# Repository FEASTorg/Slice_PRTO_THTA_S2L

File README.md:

# Prototyping Slice

THT Array/All.

BREAD slice for creating new BREAD slices.

## Introduction

[Short introduction on the project.]

## Usage

[Explain how to use the project. Include examples and screenshots if applicable.]

## Documentation

Please refer to the [docs](/docs) for more info.

---

<div align="center">
  
</div>

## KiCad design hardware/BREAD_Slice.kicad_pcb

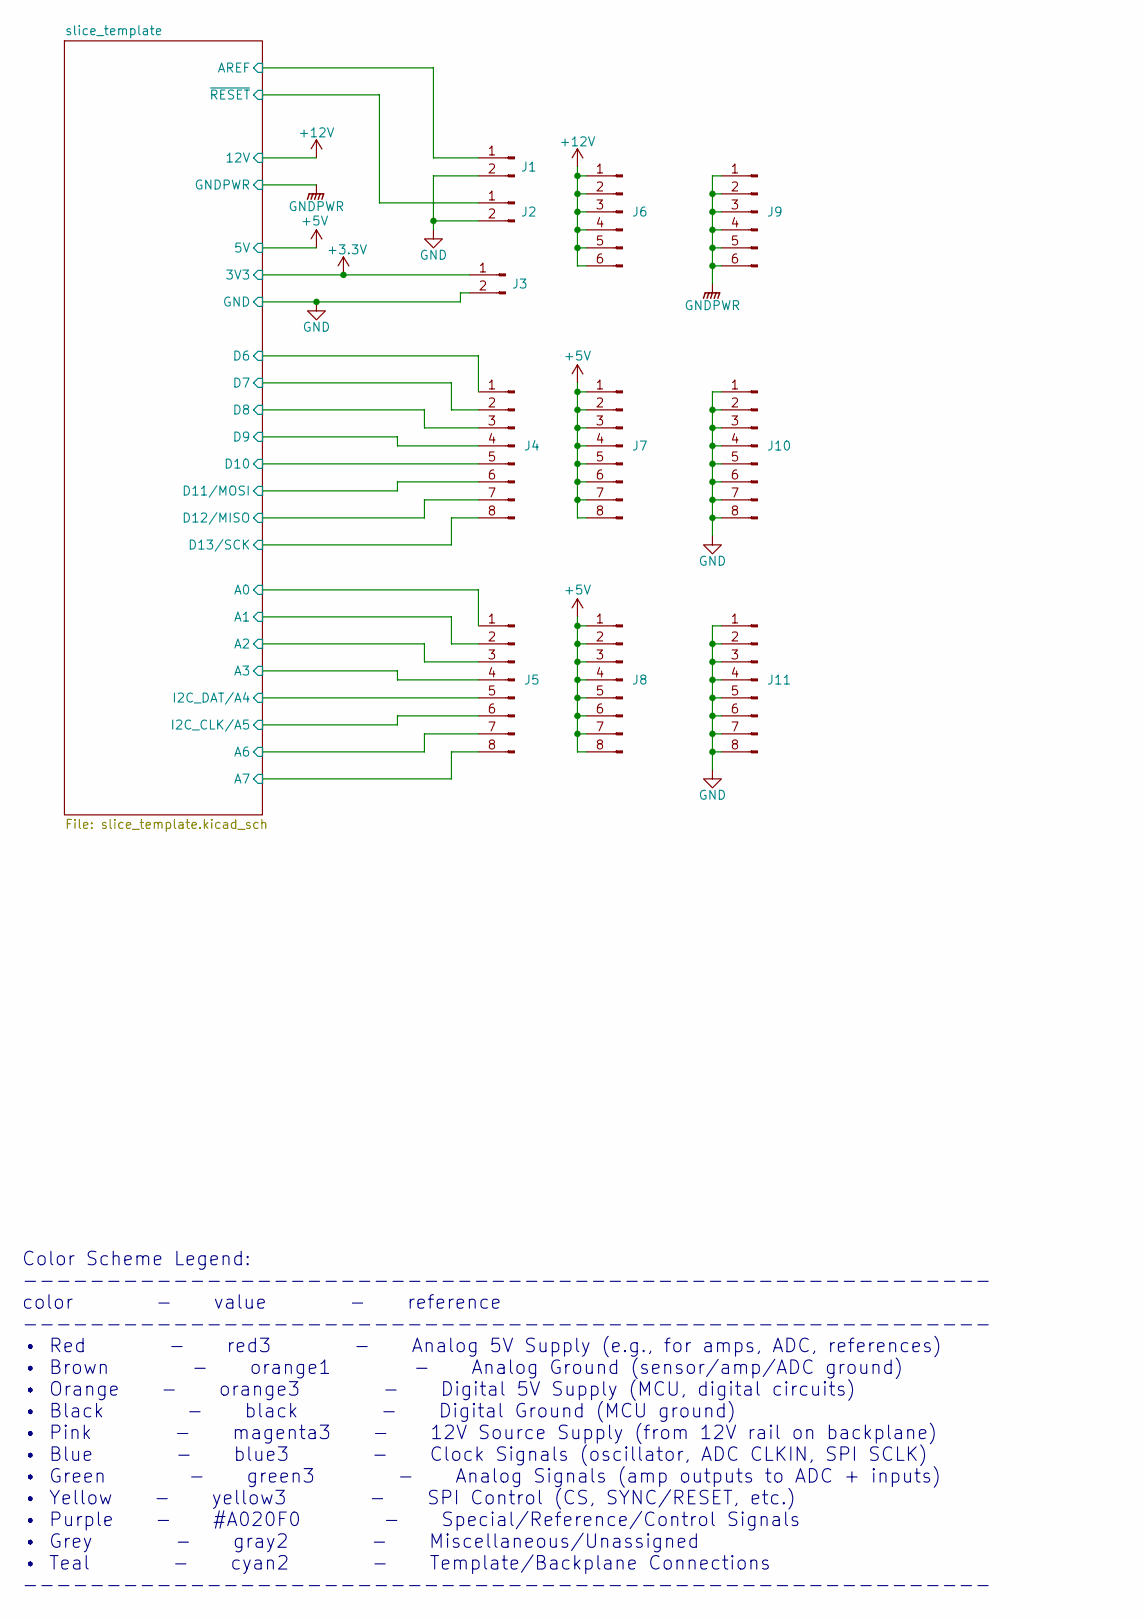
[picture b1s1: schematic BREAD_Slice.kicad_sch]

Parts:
J1, J2, J3: Conn_01x02_Pin; PinHeader_1x02_P2.54mm_Vertical
J4, J5, J7, J8, J10, J11: Conn_01x08_Pin; PinHeader_1x08_P2.54mm_Vertical
J6, J9: Conn_01x06_Pin; PinHeader_1x06_P2.54mm_Vertical

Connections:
+3.3V: J3.1; also elsewhere on the board
+5V: J7.1, J7.2, J7.3, J7.4, J7.5, J7.6, J7.7, J7.8, J8.1, J8.2, J8.3, J8.4, J8.5, J8.6, J8.7, J8.8; also elsewhere on the board
+12V: J6.1, J6.2, J6.3, J6.4, J6.5, J6.6; also elsewhere on the board
/slice_template/A0: J5.1; also elsewhere on the board
/slice_template/A1: J5.2; also elsewhere on the board
/slice_template/A2: J5.3; also elsewhere on the board
/slice_template/A3: J5.4; also elsewhere on the board
/slice_template/A6: J5.7; also elsewhere on the board
/slice_template/A7: J5.8; also elsewhere on the board
/slice_template/AREF: J1.1; also elsewhere on the board
/slice_template/D6: J4.1; also elsewhere on the board
/slice_template/D7: J4.2; also elsewhere on the board
/slice_template/D8: J4.3; also elsewhere on the board
/slice_template/D9: J4.4; also elsewhere on the board
/slice_template/D10: J4.5; also elsewhere on the board
/slice_template/D11/MOSI: J4.6; also elsewhere on the board
/slice_template/D12/MISO: J4.7; also elsewhere on the board
/slice_template/D13/SCK: J4.8; also elsewhere on the board
/slice_template/I2C_CLK/A5: J5.6; also elsewhere on the board
/slice_template/I2C_DAT/A4: J5.5; also elsewhere on the board
/slice_template/~RESET: J2.1; also elsewhere on the board
GND: J1.2, J2.2, J3.2, J10.1, J10.2, J10.3, J10.4, J10.5, J10.6, J10.7, J10.8, J11.1, J11.2, J11.3, J11.4, J11.5, J11.6, J11.7, J11.8; also elsewhere on the board
GNDPWR: J9.1, J9.2, J9.3, J9.4, J9.5, J9.6; also elsewhere on the board

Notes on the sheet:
Color Scheme Legend: ---------------------------------------------------------- color - value - reference ---------------------------------------------------------- • Red - red3 - Analog 5V Supply (e.g., for amps, ADC, references) • Brown - orange1 - Analog Ground (sensor/amp/ADC ground) • Orange -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

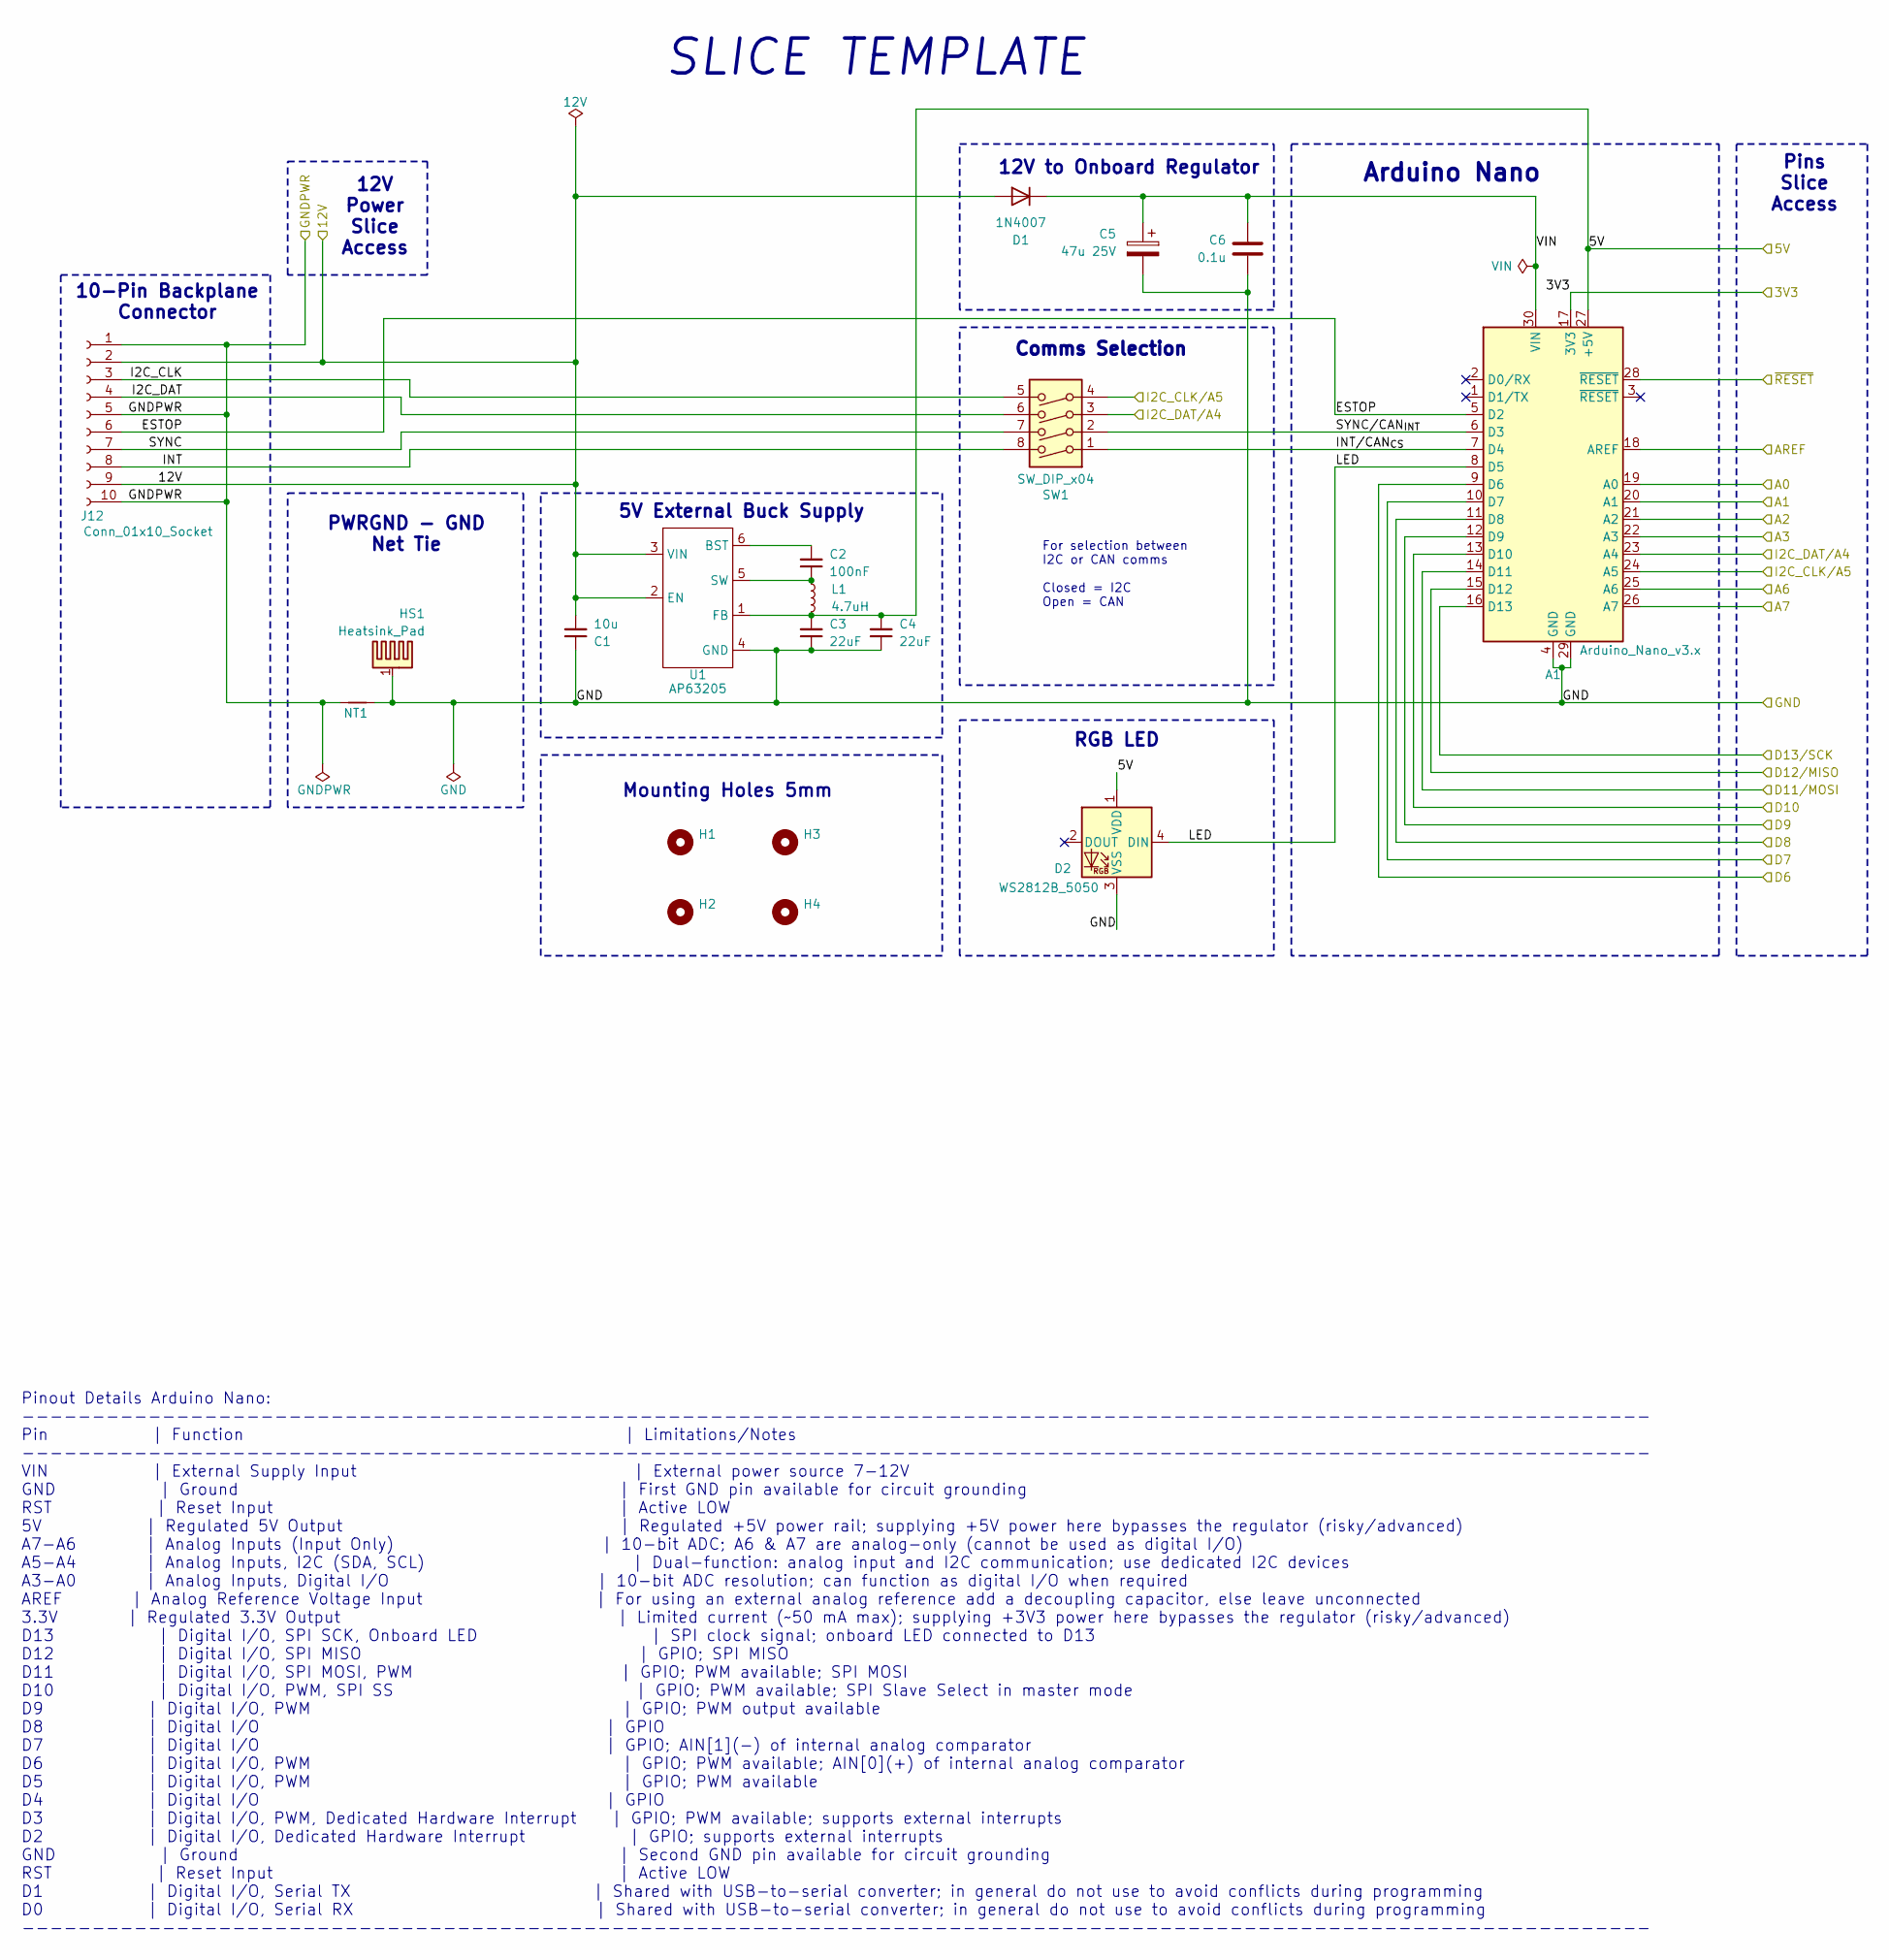
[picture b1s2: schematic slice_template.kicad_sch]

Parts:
A1: Arduino_Nano_v3.x; Arduino_Nano_Headers
C1: 10u; C_1206_3216Metric
C2: 100nF; C_1206_3216Metric
C3, C4: 22uF; C_1206_3216Metric
C5: 47u 25V; CP_Elec_6.3x7.7
C6: 0.1u; C_0805_2012Metric_Pad1.18x1.45mm_HandSolder
D1: 1N4007; D_SOD-123F
D2: WS2812B_5050; WS2812-5050-4PIN
H1, H2, H3, H4: MountingHole; MountingHole_5mm
HS1: Heatsink_Pad; Thermal_Pad
J12: Conn_01x10_Socket; PinSocket_1x10_P2.54mm_Horizontal
L1: 4.7uH; L_1210_3225Metric
NT1: NetTie_2; NetTie-2_SMD_Pad2.0mm
SW1: SW_DIP_x04; SW_DIP_SPSTx04_Slide_9.78x12.34mm_W8.61mm_P2.54mm
U1: AP63205; SOIC_05WU-7_DIO

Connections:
+3.3V: A1.17 (3V3); also elsewhere on the board
+5V: A1.27 (+5V), C3.2, C4.2, D2.1 (VDD), L1.2, U1.1 (FB); also elsewhere on the board
+12V: C1.2, D1.2 (A), J12.2, J12.9, U1.2 (EN), U1.3 (VIN); also elsewhere on the board
/slice_template/A0: A1.19 (A0); also elsewhere on the board
/slice_template/A1: A1.20 (A1); also elsewhere on the board
/slice_template/A2: A1.21 (A2); also elsewhere on the board
/slice_template/A3: A1.22 (A3); also elsewhere on the board
/slice_template/A6: A1.25 (A6); also elsewhere on the board
/slice_template/A7: A1.26 (A7); also elsewhere on the board
/slice_template/AREF: A1.18 (AREF); also elsewhere on the board
/slice_template/D6: A1.9 (D6); also elsewhere on the board
/slice_template/D7: A1.10 (D7); also elsewhere on the board
/slice_template/D8: A1.11 (D8); also elsewhere on the board
/slice_template/D9: A1.12 (D9); also elsewhere on the board
/slice_template/D10: A1.13 (D10); also elsewhere on the board
/slice_template/D11/MOSI: A1.14 (D11); also elsewhere on the board
/slice_template/D12/MISO: A1.15 (D12); also elsewhere on the board
/slice_template/D13/SCK: A1.16 (D13); also elsewhere on the board
/slice_template/ESTOP: A1.5 (D2), J12.6
/slice_template/I2C_CLK: J12.3, SW1.5
/slice_template/I2C_CLK/A5: A1.24 (A5), SW1.4; also elsewhere on the board
/slice_template/I2C_DAT: J12.4, SW1.6
/slice_template/I2C_DAT/A4: A1.23 (A4), SW1.3; also elsewhere on the board
/slice_template/INT: J12.8, SW1.8
/slice_template/INT/CAN_{CS}: A1.7 (D4), SW1.1
/slice_template/LED: A1.8 (D5), D2.4 (DIN)
/slice_template/SYNC: J12.7, SW1.7
/slice_template/SYNC/CAN_{INT}: A1.6 (D3), SW1.2
/slice_template/VIN: A1.30 (VIN), C5.1, C6.1, D1.1 (K)
/slice_template/~RESET: A1.28 (~RESET); also elsewhere on the board
GND: A1.4 (GND), A1.29 (GND), C1.1, C3.1, C4.1, C5.2, C6.2, D2.3 (VSS), HS1.1, NT1.1, U1.4 (GND); also elsewhere on the board
GNDPWR: J12.1, J12.5, J12.10, NT1.2; also elsewhere on the board
unnamed: C2.2, U1.6 (BST)
unnamed: C2.1, L1.1, U1.5 (SW)

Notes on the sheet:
Pins Slice Access
10-Pin Backplane Connector
PWRGND - GND Net Tie
SLICE TEMPLATE
RGB LED
Pinout Details Arduino Nano: -------------------------------------------------------------------------------------------------------------------- Pin | Function | Limitations/Notes -------------------------------------------------------------------------------------------------------------------- V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
Comms Selection
Mounting Holes 5mm
12V Power Slice Access
For selection between I2C or CAN comms Closed = I2C Open = CAN
Arduino Nano
12V to Onboard Regulator
5V External Buck Supply

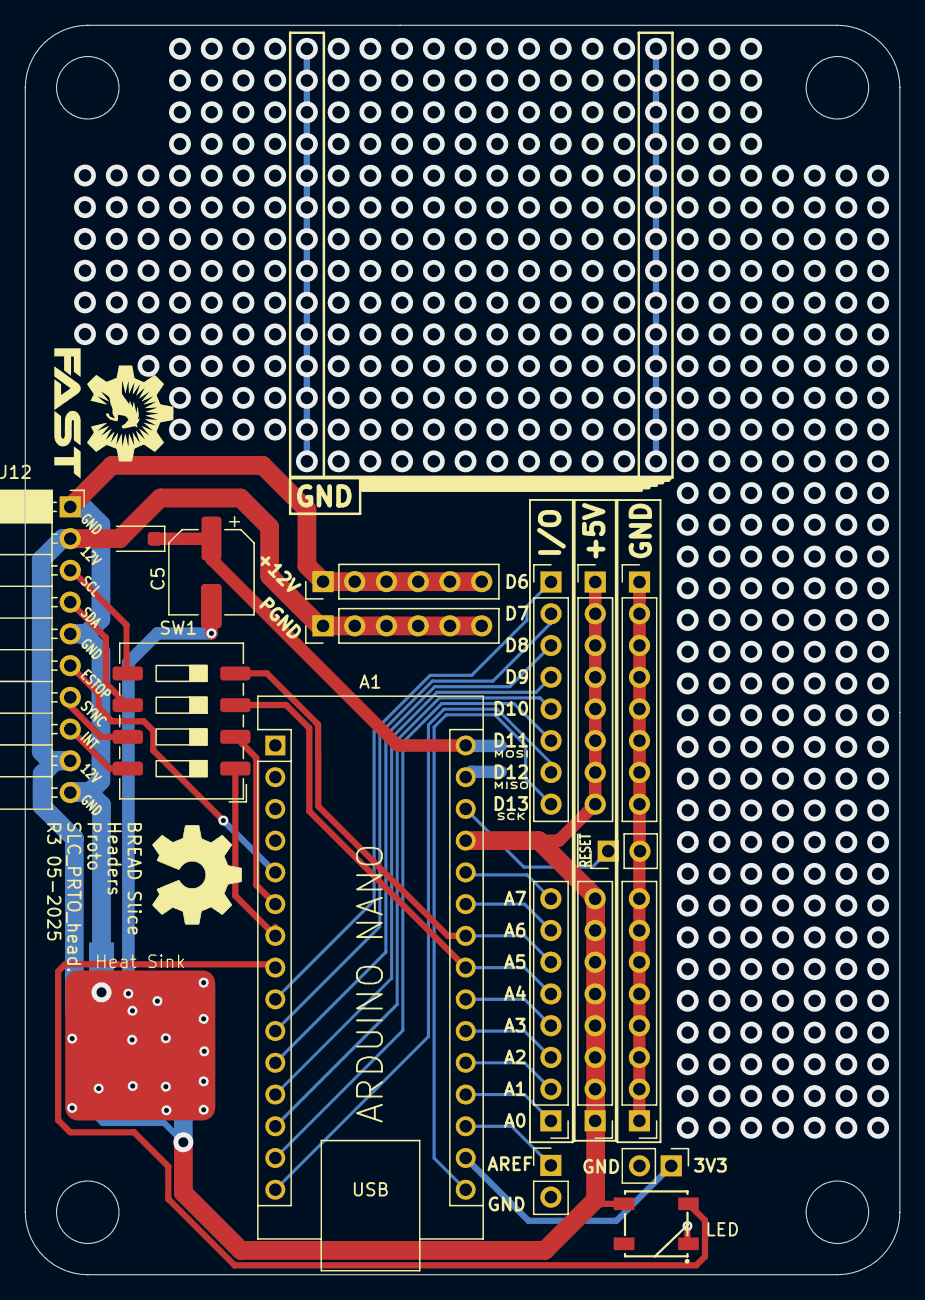
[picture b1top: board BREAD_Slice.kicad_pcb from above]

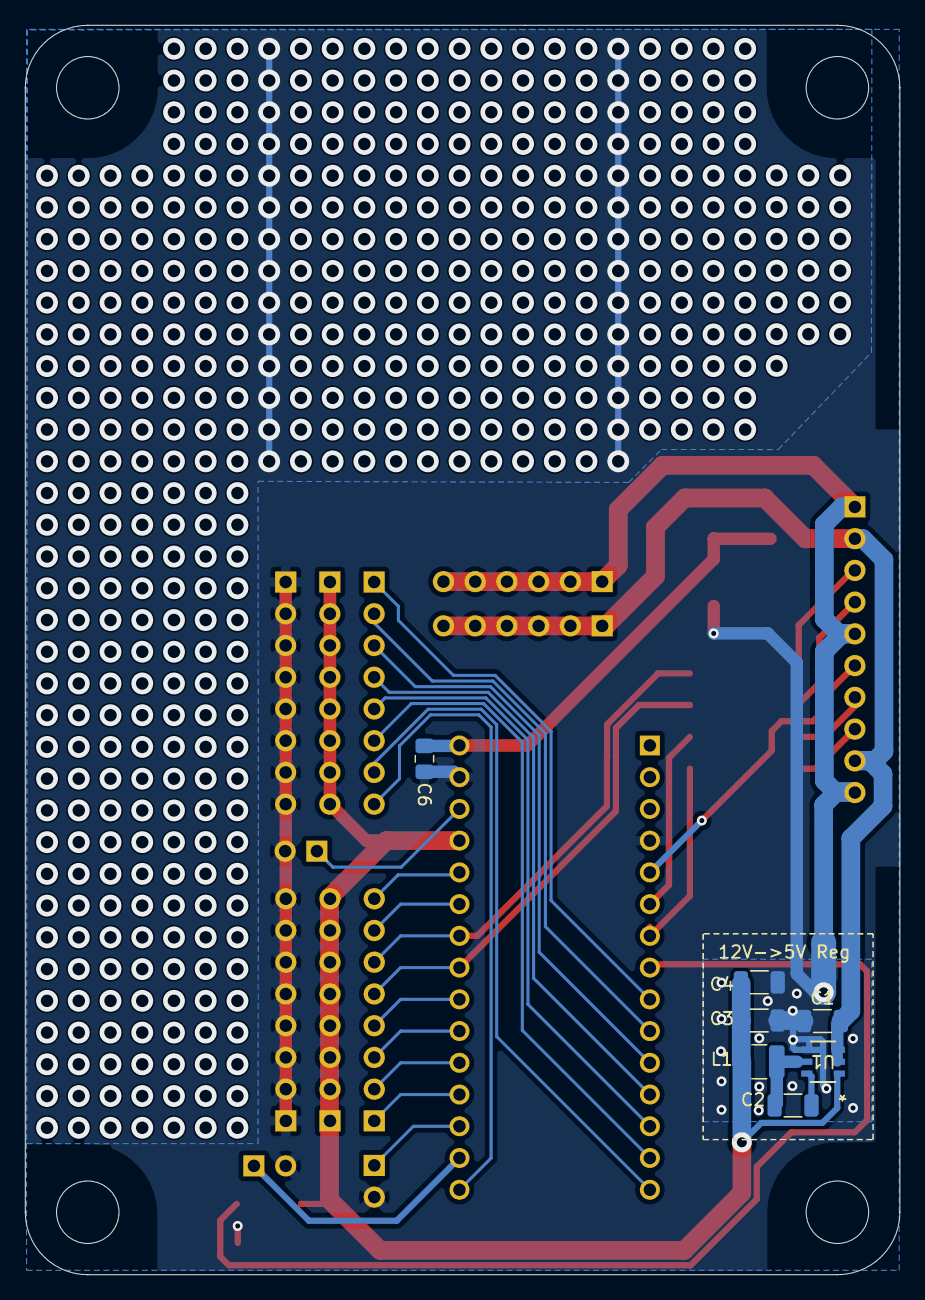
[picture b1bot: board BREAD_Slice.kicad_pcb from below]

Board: 2 copper layers, 70.0 x 100.0 mm, 31 parts (8 on the bottom side), 34 nets.

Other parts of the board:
Ref**: Val**; OSHW_Logo_8mm

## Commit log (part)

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2025-09-24 initial commit after split
2025-09-24 ci: initial commit of workflow after split
2025-09-24 📄 KiBot index + board renders (auto)
2026-01-26 review and revise board and update footprints
2026-01-26 stop tracking backups
2026-01-26 standard ignore
2026-04-20 refactor: org casing rename from 'FEASTorg' to 'feastorg'
2026-05-20 Add slice.yaml manifest (schema v1.0)
2026-05-24 Add standardized TODO.md with Pass 1/Pass 2 structure
